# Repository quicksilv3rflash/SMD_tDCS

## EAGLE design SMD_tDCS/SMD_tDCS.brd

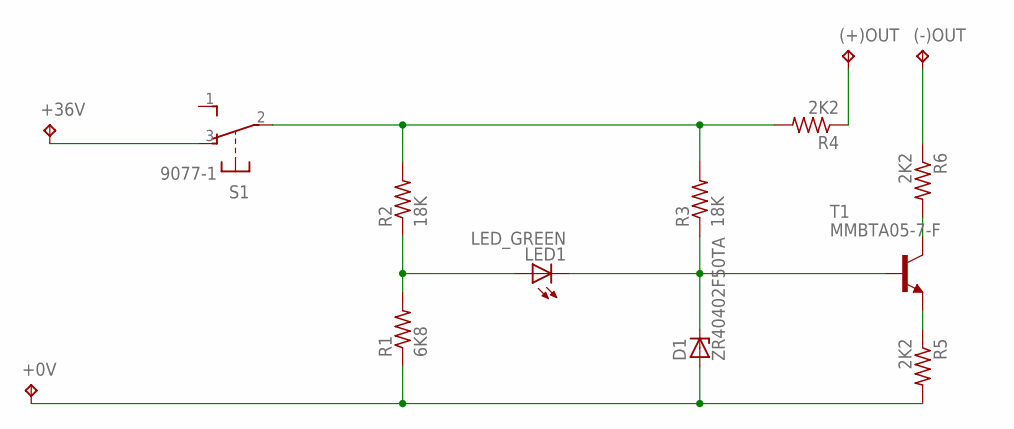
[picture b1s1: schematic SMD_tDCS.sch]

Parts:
(+)OUT: TPTP20SQ; TP20SQ
(-)OUT: TPTP20SQ; TP20SQ
+0V, +36V: TPTP20SQ; TP20SQ
D1: ZR40402F50TA; SOT23
LED1: LED_GREEN; CHIP-LED0805
R1: 6K8; R0402
R2, R3: 18K; R0603
R4, R5, R6: 2K2; R2512
S1: 9077-1
T1: MMBTA05-7-F; SOT23-BEC

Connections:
unnamed: LED1.A, R1.2, R2.1
unnamed: R6.2, T1.C
unnamed: +0V.TP, D1.1 (A), R1.1, R5.2
unnamed: (+)OUT.TP, R4.1
unnamed: (-)OUT.TP, R6.1
unnamed: R5.1, T1.E
unnamed: +36V.TP, S1.3 (O)
unnamed: R2.2, R3.2, R4.2, S1.2
unnamed: D1.3 (C), LED1.C, R3.1, T1.B

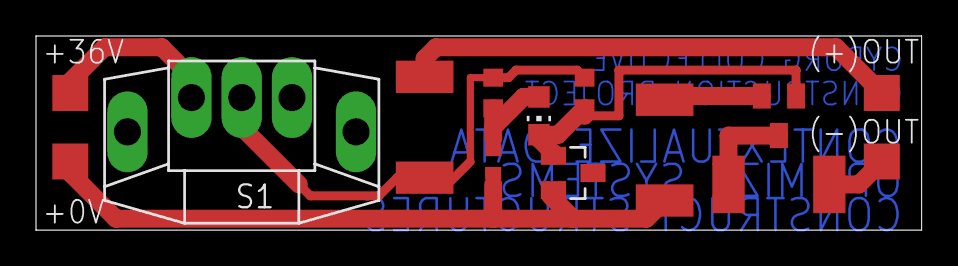
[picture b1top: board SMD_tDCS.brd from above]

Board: 2 copper layers, 49.2 x 10.8 mm, 14 parts (0 on the bottom side), 9 nets.

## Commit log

2016-02-10 :confetti_ball: Added .gitattributes & .gitignore files
2016-02-10 now with files
2016-02-10 zip
    zip
